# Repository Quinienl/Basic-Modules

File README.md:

These modules are tested

- Multiple
- Buffered Multiple
- Switch

These files can be used to build your own PCB's and Panels

More info on my site

[Quinie Basic Modules](https://www.quinie.nl/the-basic-modules/).

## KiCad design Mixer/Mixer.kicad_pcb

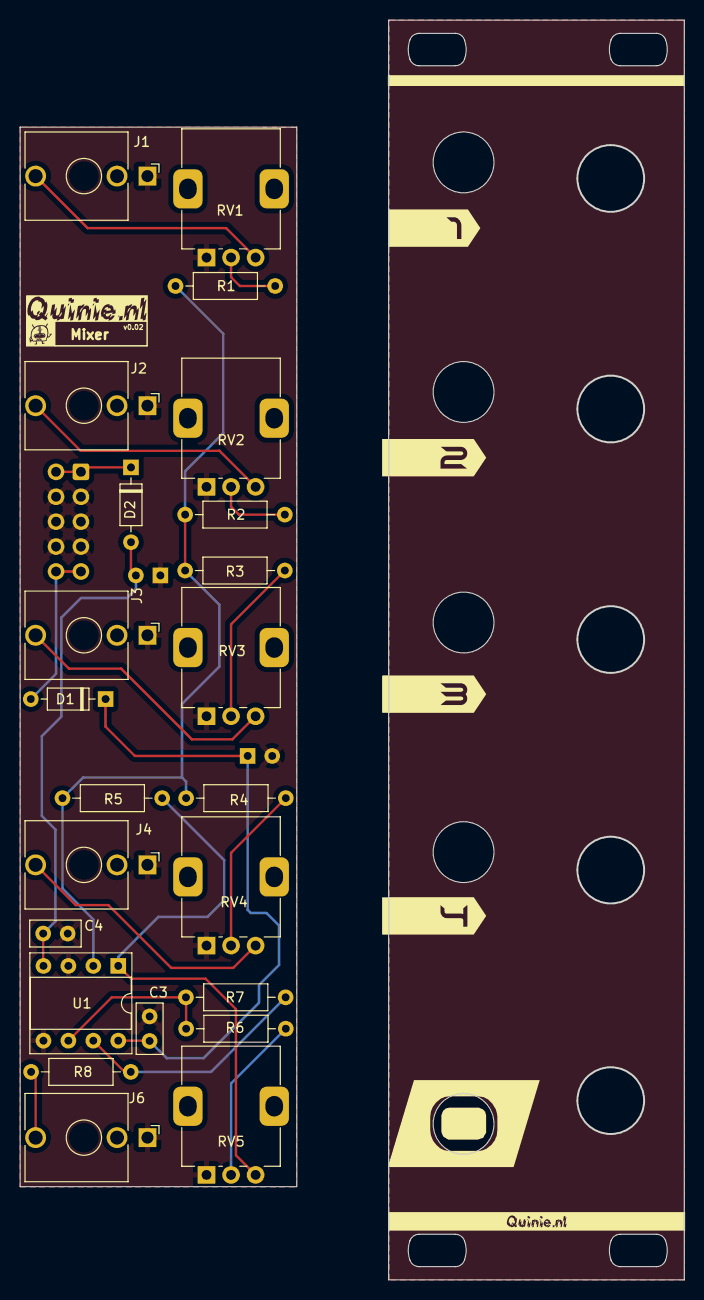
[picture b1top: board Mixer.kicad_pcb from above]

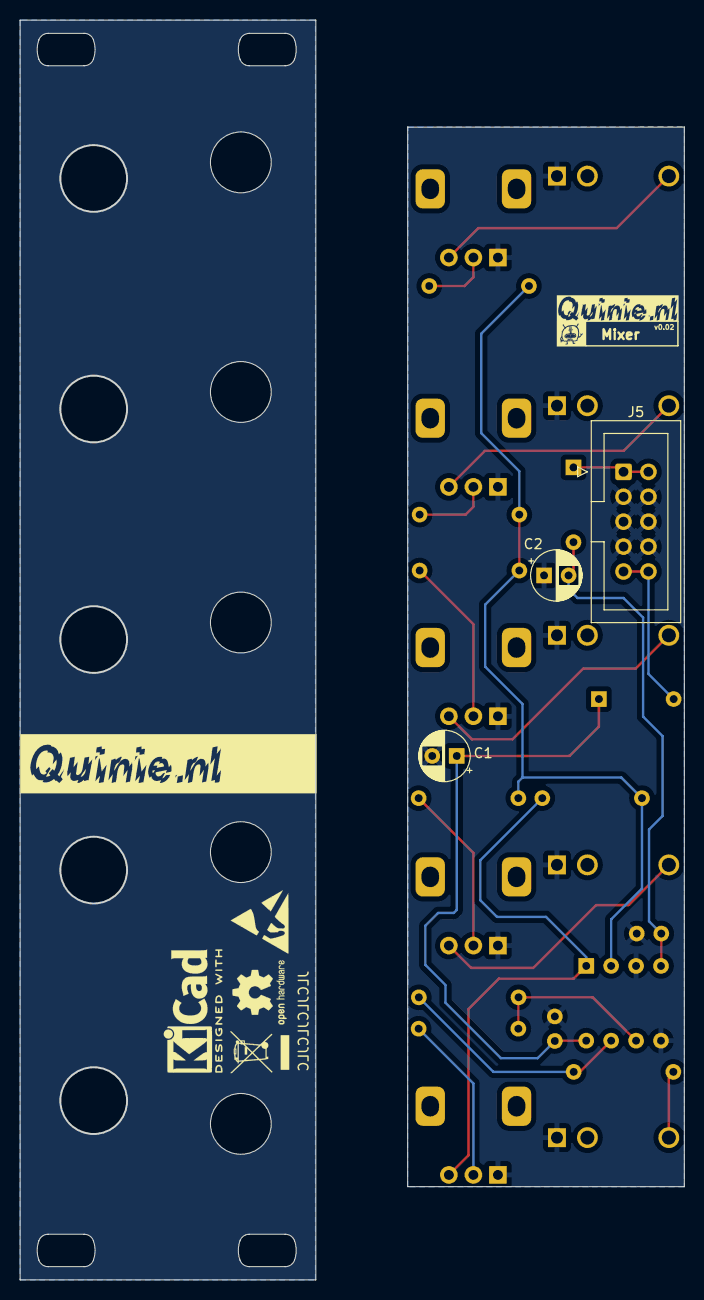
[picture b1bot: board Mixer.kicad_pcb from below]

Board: 2 copper layers, 67.6 x 128.3 mm, 38 parts (6 on the bottom side), 19 nets.

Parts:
C1, C2: 10uf; CP_Radial_D5.0mm_P2.50mm
C3, C4: C; C_Disc_D5.0mm_W2.5mm_P2.50mm
D1, D2: 1n4148; D_DO-35_SOD27_P7.62mm_Horizontal
J1, J2, J3, J4, J6: AudioJack2_SwitchT; Jack_3.5mm_QingPu_WQP-PJ398SM_Vertical_CircularHoles
J5: Conn_02x05_Odd_Even; IDC-Header_2x05_P2.54mm_Vertical
R1, R2, R3, R4, R5, R6, R7: 100k; R_Axial_DIN0207_L6.3mm_D2.5mm_P10.16mm_Horizontal
R8: 1k; R_Axial_DIN0207_L6.3mm_D2.5mm_P10.16mm_Horizontal
RV1, RV2, RV3, RV4, RV5: R_Potentiometer; Potentiometer_Alps_RK09K_Single_Vertical
U1: TL072; DIP-8_W7.62mm_Socket
kibuzzard-65A30B0C: G***; kibuzzard-65A30B0C
kibuzzard-65A30B02: G***; kibuzzard-65A30B02
kibuzzard-65A30B14: G***; kibuzzard-65A30B14
kibuzzard-65A30BCA: G***; kibuzzard-65A30BCA
kibuzzard-63729A5C, kibuzzard-63729A5C#2: G***; kibuzzard-63729A5C
kibuzzard-63947F16: G***; kibuzzard-63947F16
kibuzzard-63948EE9: G***; kibuzzard-63948EE9
kibuzzard-639724AE: G***; kibuzzard-639724AE
kibuzzard-63663374, kibuzzard-63663374#2: G***; kibuzzard-63663374
kibuzzard-63949171: G***; kibuzzard-63949171

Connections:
+12V: C1.1, C3.2, D1.1 (K), U1.8 (V+)
-12V: C2.2, C4.2, D2.2 (A), U1.4 (V-)
GND: C1.2, C2.1, C3.1, C4.1, J1.S, J2.S, J3.S, J4.S, J5.3, J5.4, J5.5, J5.6, J5.7, J5.8, J6.S, RV1.1, RV2.1, RV3.1, RV4.1, RV5.1, U1.3 (+), U1.5 (+)
unnamed: D1.2 (A), J5.9, J5.10
unnamed: D2.1 (K), J5.1, J5.2
unnamed: J1.T, RV1.3
unnamed: J2.T, RV2.3
unnamed: J3.T, RV3.3
unnamed: J4.T, RV4.3
unnamed: J6.T, R8.1
unnamed: R1.1, RV1.2
unnamed: R2.1, RV2.2
unnamed: R3.1, RV3.2
unnamed: R4.1, RV4.2
unnamed: R5.1, RV5.3, U1.1
unnamed: R6.1, RV5.2
unnamed: R7.1, R8.2, U1.7
unnamed: R1.2, R2.2, R3.2, R4.2, R5.2, U1.2 (-)
unnamed: R6.2, R7.2, U1.6 (-)

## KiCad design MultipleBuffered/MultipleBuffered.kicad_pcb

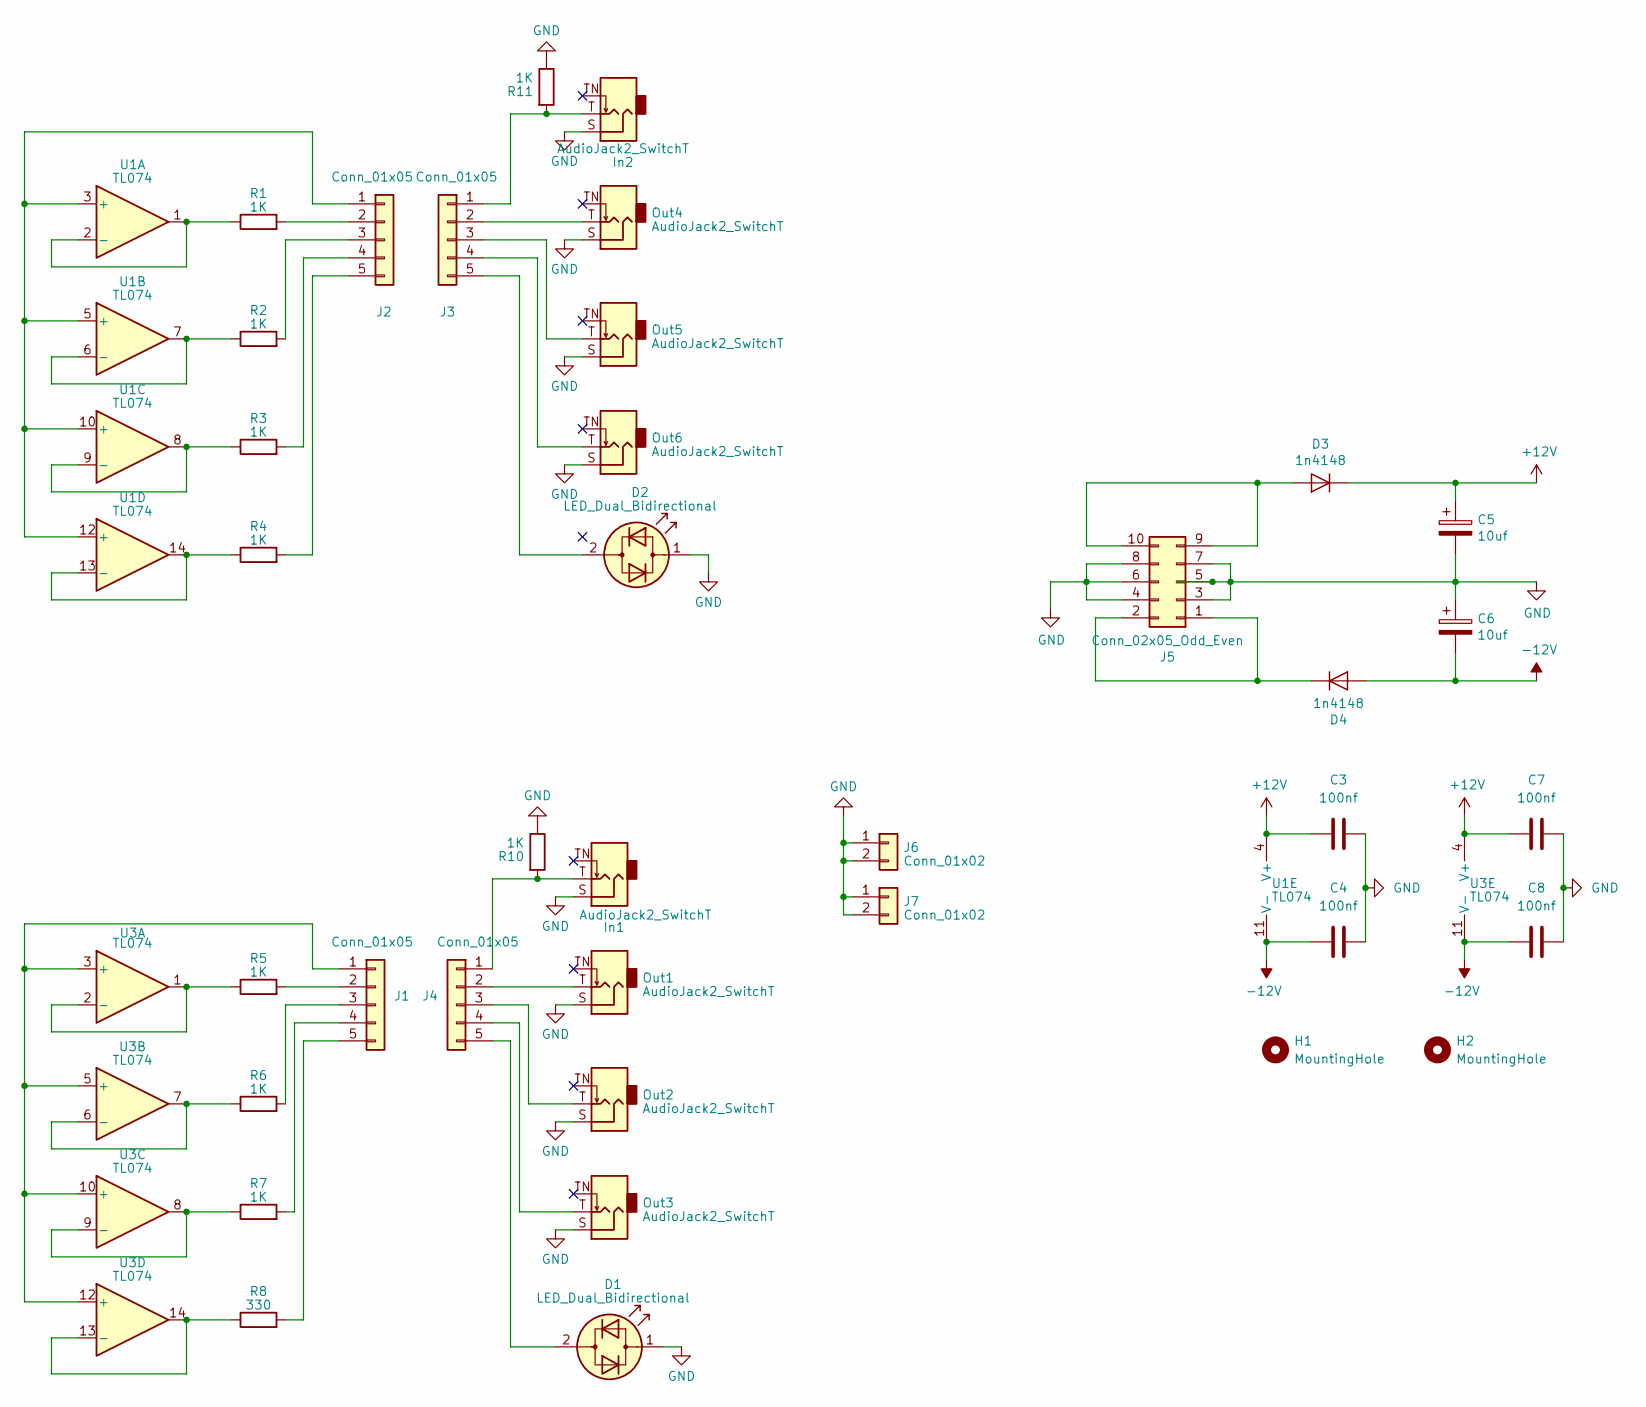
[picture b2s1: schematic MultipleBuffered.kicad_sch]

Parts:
C3, C4, C7, C8: 100nf; C_Disc_D5.0mm_W2.5mm_P2.50mm
C5, C6: 10uf; CP_Radial_D5.0mm_P2.50mm
D1, D2: LED_Dual_Bidirectional; LED_D3.0mm
D3, D4: 1n4148; D_DO-35_SOD27_P7.62mm_Horizontal
H1, H2: MountingHole; MountingHole_3.2mm_M3
In1, In2: AudioJack2_SwitchT; Jack_3.5mm_QingPu_WQP-PJ398SM_Vertical_CircularHoles
J1, J2: Conn_01x05; PinHeader_1x05_P2.54mm_Vertical
J3, J4: Conn_01x05; PinSocket_1x05_P2.54mm_Vertical
J5: Conn_02x05_Odd_Even; IDC-Header_2x05_P2.54mm_Vertical
J6: Conn_01x02; PinHeader_1x02_P2.54mm_Vertical
J7: Conn_01x02; PinSocket_1x02_P2.54mm_Vertical
Out1, Out2, Out3, Out4, Out5, Out6: AudioJack2_SwitchT; Jack_3.5mm_QingPu_WQP-PJ398SM_Vertical_CircularHoles
R1, R2, R3, R4, R5, R6, R7, R11: 1K; R_Axial_DIN0207_L6.3mm_D2.5mm_P7.62mm_Horizontal
R8: 330; R_Axial_DIN0207_L6.3mm_D2.5mm_P7.62mm_Horizontal
R10: 1K; R_Axial_DIN0207_L6.3mm_D2.5mm_P2.54mm_Vertical
U1, U3: TL074; DIP-14_W7.62mm_Socket

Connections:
+12V: C3.1, C5.1, C7.1, D3.1 (K), U1.4 (V+), U3.4 (V+)
-12V: C4.1, C6.2, C8.1, D4.2 (A), U1.11 (V-), U3.11 (V-)
GND: C3.2, C4.2, C5.2, C6.1, C7.2, C8.2, D1.1 (KA), D2.1 (KA), In1.S, In2.S, J5.3, J5.4, J5.5, J5.6, J5.7, J5.8, J6.1, J6.2, J7.1, J7.2, Out1.S, Out2.S, Out3.S, Out4.S, Out5.S, Out6.S, R10.1, R11.1
unnamed: D1.2 (AK), J4.5
unnamed: D2.2 (AK), J3.5
unnamed: D3.2 (A), J5.9, J5.10
unnamed: D4.1 (K), J5.1, J5.2
unnamed: J1.1, U3.3 (+), U3.5 (+), U3.10 (+), U3.12 (+)
unnamed: J1.2, R5.2
unnamed: J1.3, R6.2
unnamed: J1.4, R7.2
unnamed: J1.5, R8.2
unnamed: J2.1, U1.3 (+), U1.5 (+), U1.10 (+), U1.12 (+)
unnamed: J2.2, R1.2
unnamed: J2.3, R2.2
unnamed: J2.4, R3.2
unnamed: J2.5, R4.2
unnamed: In2.T, J3.1, R11.2
unnamed: J3.2, Out4.T
unnamed: J3.3, Out5.T
unnamed: J3.4, Out6.T
unnamed: In1.T, J4.1, R10.2
unnamed: J4.2, Out1.T
unnamed: J4.3, Out2.T
unnamed: J4.4, Out3.T
unnamed: R1.1, U1.1, U1.2 (-)
unnamed: R2.1, U1.6 (-), U1.7
unnamed: R3.1, U1.8, U1.9 (-)
unnamed: R4.1, U1.13 (-), U1.14
unnamed: R5.1, U3.1, U3.2 (-)
unnamed: R6.1, U3.6 (-), U3.7
unnamed: R7.1, U3.8, U3.9 (-)
unnamed: R8.1, U3.13 (-), U3.14

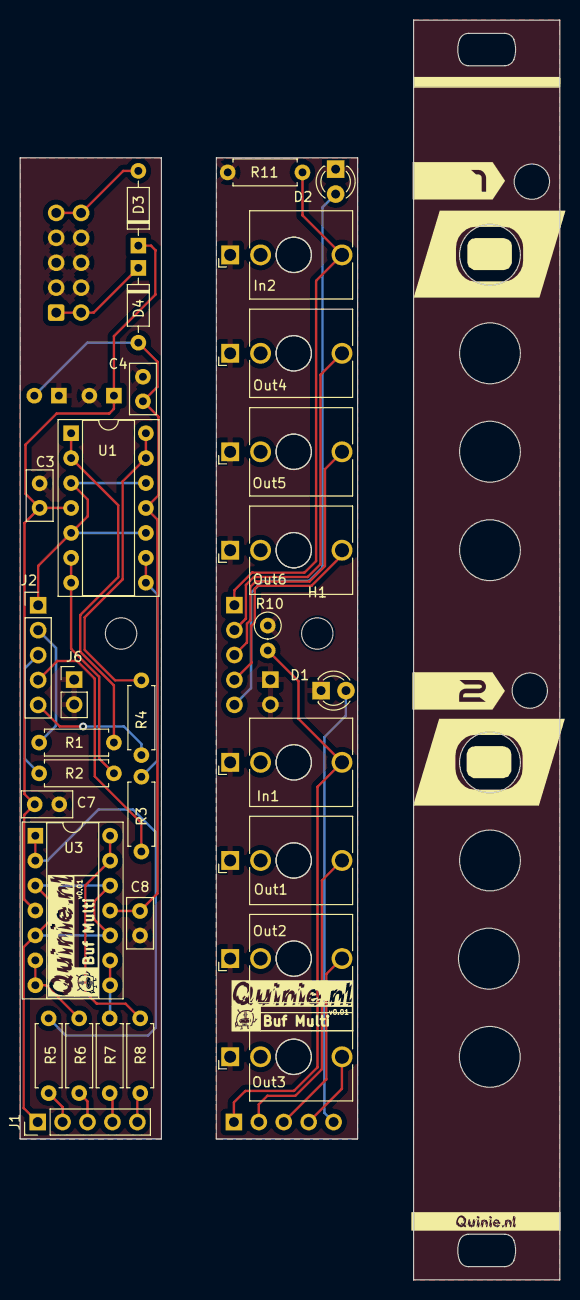
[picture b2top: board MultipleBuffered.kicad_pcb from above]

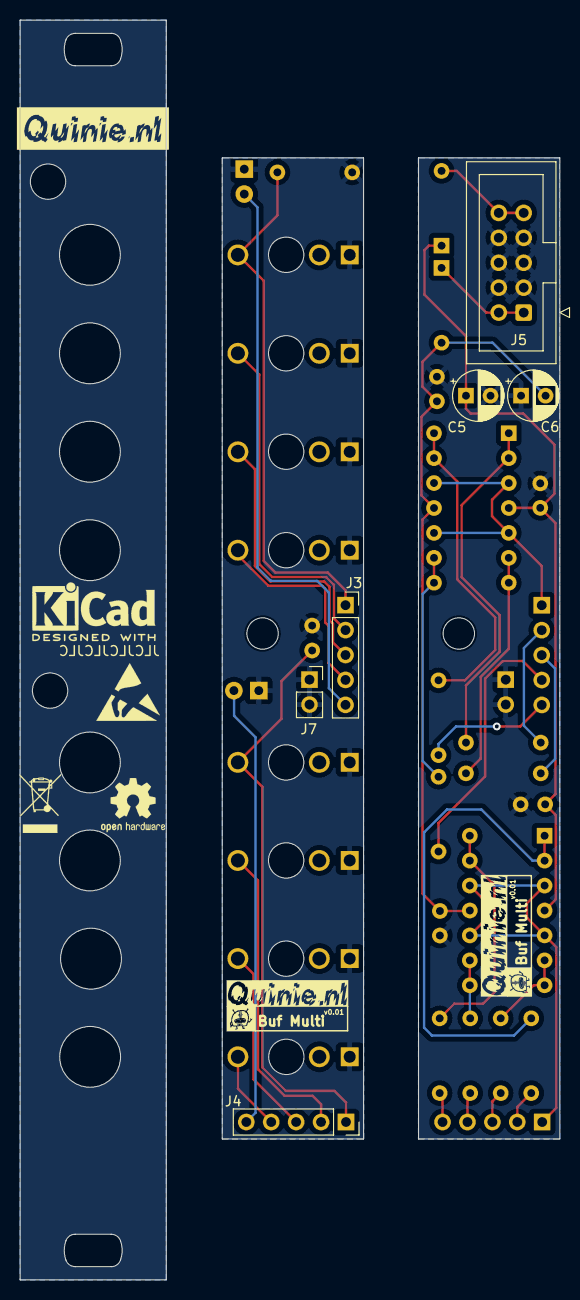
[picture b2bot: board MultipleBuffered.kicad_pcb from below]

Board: 2 copper layers, 55.0 x 128.4 mm, 54 parts (11 on the bottom side), 33 nets.

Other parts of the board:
kibuzzard-656B60C2: G***; kibuzzard-656B60C2
kibuzzard-656B617B: G***; kibuzzard-656B617B
kibuzzard-656CA602: G***; kibuzzard-656CA602
kibuzzard-656CA711: G***; kibuzzard-656CA711
kibuzzard-63729A5C, kibuzzard-63729A5C#2, kibuzzard-63729A5C#3, kibuzzard-63729A5C#4: G***; kibuzzard-63729A5C
kibuzzard-63948EE9: G***; kibuzzard-63948EE9
kibuzzard-63663374, kibuzzard-63663374#2, kibuzzard-63663374#3, kibuzzard-63663374#4: G***; kibuzzard-63663374
kibuzzard-63949171, kibuzzard-63949171#2: G***; kibuzzard-63949171

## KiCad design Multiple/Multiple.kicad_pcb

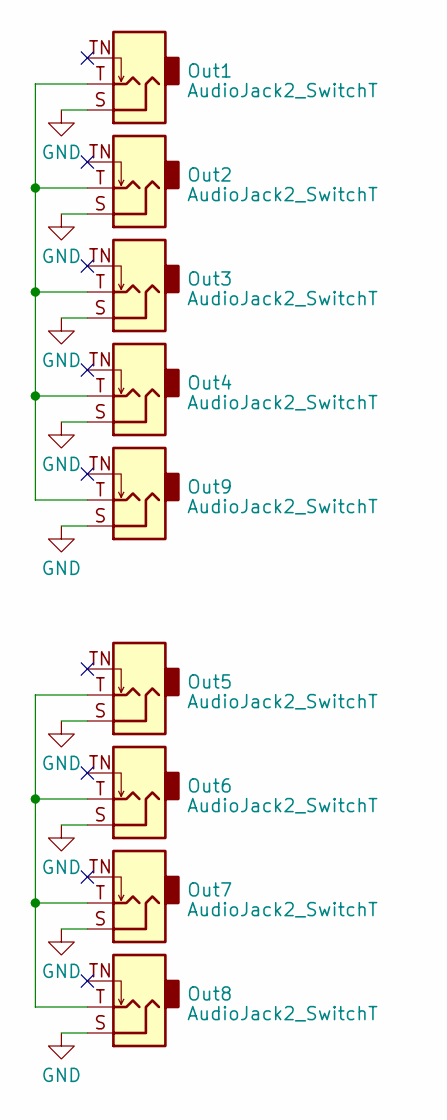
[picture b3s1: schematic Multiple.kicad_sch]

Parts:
Out1, Out2, Out3, Out4, Out5, Out6, Out7, Out8, Out9: AudioJack2_SwitchT; Jack_3.5mm_QingPu_WQP-PJ398SM_Vertical_CircularHoles

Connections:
GND: Out1.S, Out2.S, Out3.S, Out4.S, Out5.S, Out6.S, Out7.S, Out8.S, Out9.S
unnamed: Out1.T, Out2.T, Out3.T, Out4.T, Out9.T
unnamed: Out5.T, Out6.T, Out7.T, Out8.T

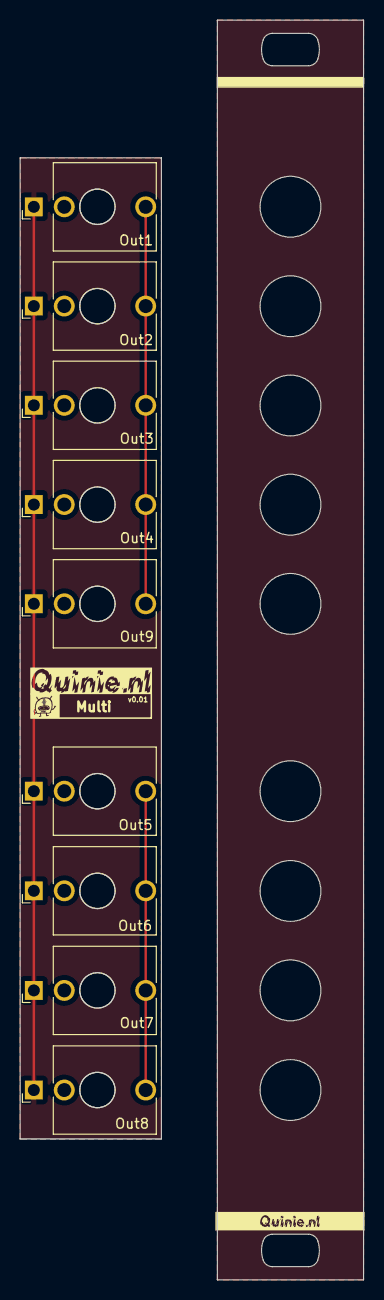
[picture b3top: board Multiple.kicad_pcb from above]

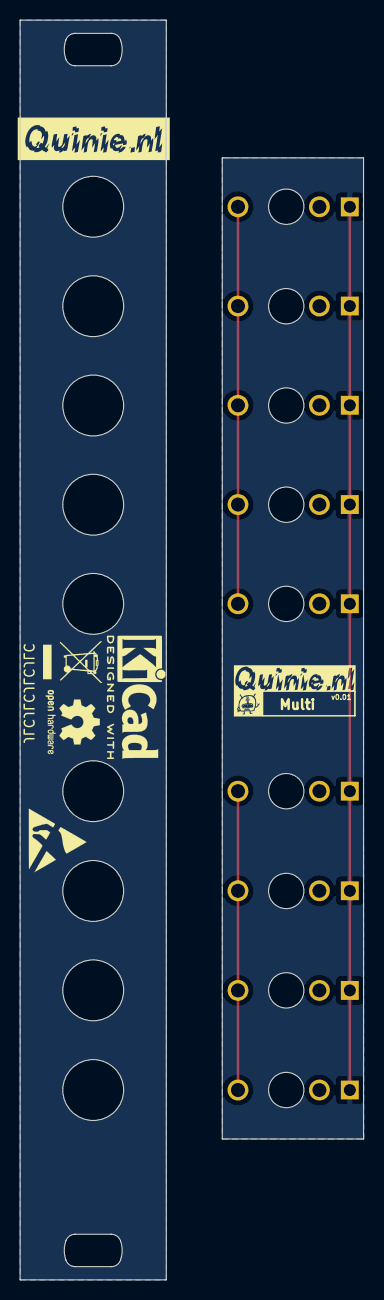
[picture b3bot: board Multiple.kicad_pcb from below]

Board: 2 copper layers, 35.0 x 128.4 mm, 16 parts (3 on the bottom side), 3 nets.

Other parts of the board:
kibuzzard-656B60C2: G***; kibuzzard-656B60C2
kibuzzard-656B617B: G***; kibuzzard-656B617B
kibuzzard-656B6089: G***; kibuzzard-656B6089
kibuzzard-63729A5C, kibuzzard-63729A5C#2: G***; kibuzzard-63729A5C
kibuzzard-63663374, kibuzzard-63663374#2: G***; kibuzzard-63663374

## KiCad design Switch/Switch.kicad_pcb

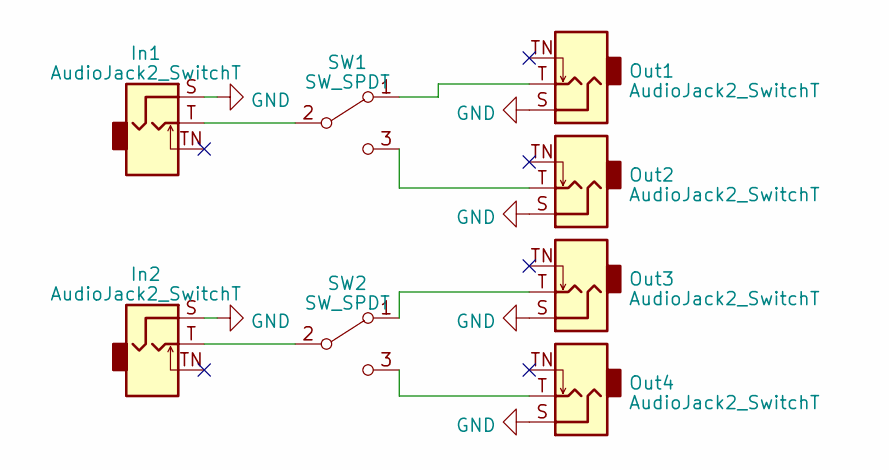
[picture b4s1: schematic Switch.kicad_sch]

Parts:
In1, In2: AudioJack2_SwitchT; Jack_3.5mm_QingPu_WQP-PJ398SM_Vertical_CircularHoles
Out1, Out2, Out3, Out4: AudioJack2_SwitchT; Jack_3.5mm_QingPu_WQP-PJ398SM_Vertical_CircularHoles
SW1, SW2: SW_SPDT; SW_100SP3T1B1M2QEH

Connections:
GND: In1.S, In2.S, Out1.S, Out2.S, Out3.S, Out4.S
unnamed: Out1.T, SW1.1 (A)
unnamed: In1.T, SW1.2 (B)
unnamed: Out2.T, SW1.3 (C)
unnamed: Out3.T, SW2.1 (A)
unnamed: In2.T, SW2.2 (B)
unnamed: Out4.T, SW2.3 (C)

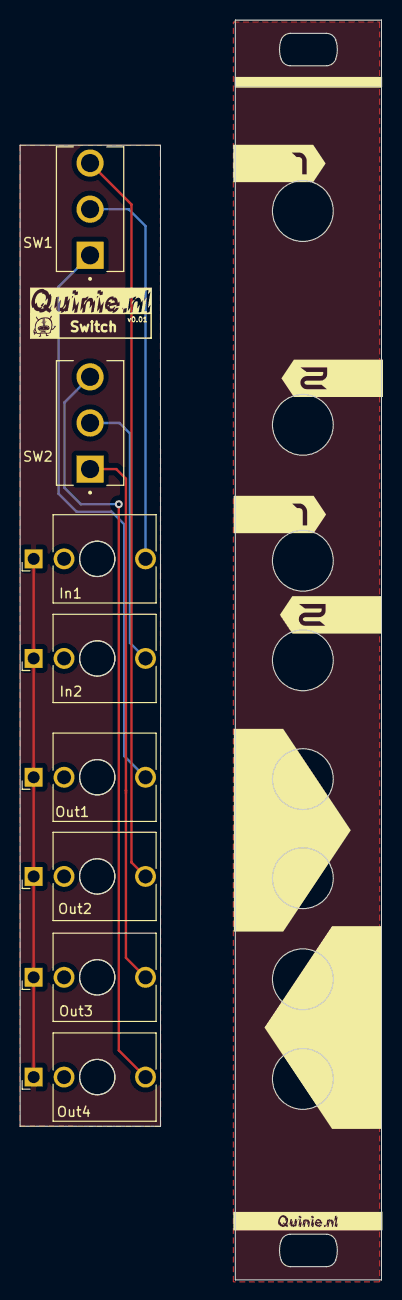
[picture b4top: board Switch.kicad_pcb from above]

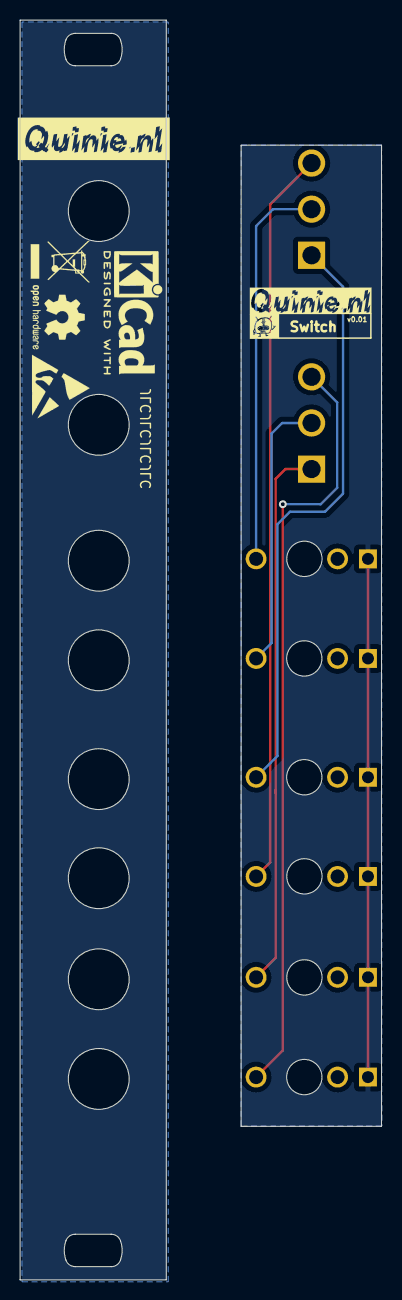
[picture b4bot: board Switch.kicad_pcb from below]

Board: 2 copper layers, 36.8 x 128.4 mm, 21 parts (3 on the bottom side), 7 nets.

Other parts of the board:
kibuzzard-656B60C2: G***; kibuzzard-656B60C2
kibuzzard-656B617B: G***; kibuzzard-656B617B
kibuzzard-656C56A9: G***; kibuzzard-656C56A9
kibuzzard-63729A5C, kibuzzard-63729A5C#2: G***; kibuzzard-63729A5C
kibuzzard-63920CDF, kibuzzard-63920CDF#2: G***; kibuzzard-63920CDF
kibuzzard-63948EC7, kibuzzard-63948EC7#2: G***; kibuzzard-63948EC7
kibuzzard-63948EE9, kibuzzard-63948EE9#2: G***; kibuzzard-63948EE9
kibuzzard-63663374, kibuzzard-63663374#2: G***; kibuzzard-63663374

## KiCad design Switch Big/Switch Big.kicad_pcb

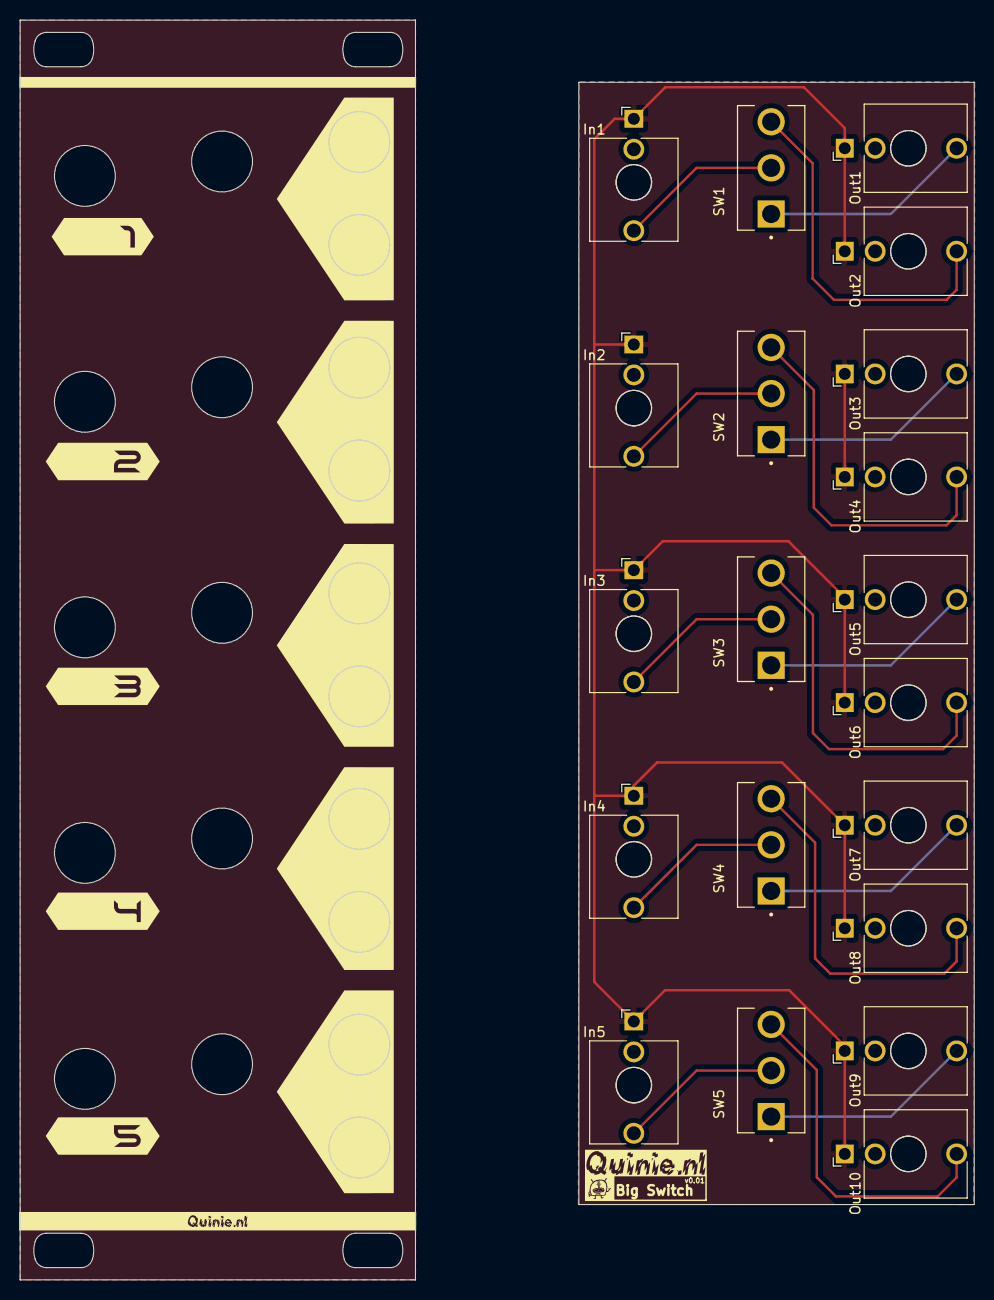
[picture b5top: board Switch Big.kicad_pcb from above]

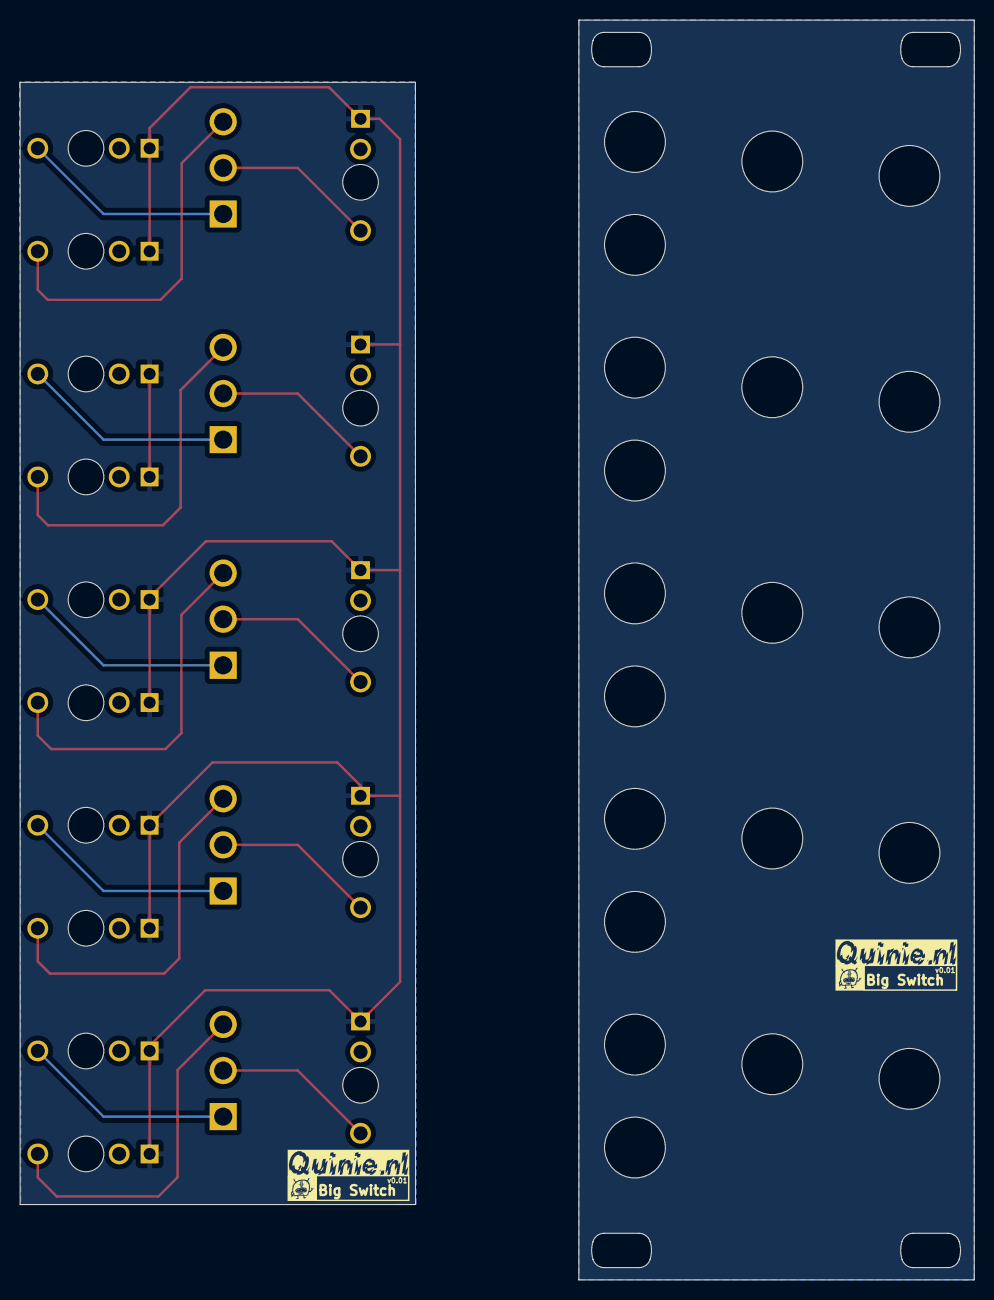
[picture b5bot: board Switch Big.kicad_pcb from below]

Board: 2 copper layers, 97.3 x 128.4 mm, 38 parts (4 on the bottom side), 16 nets.

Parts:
In1, In2, In3, In4, In5: AudioJack2_SwitchT; Jack_3.5mm_QingPu_WQP-PJ398SM_Vertical_CircularHoles
Out1, Out2, Out3, Out4, Out5, Out6, Out7, Out8, Out9, Out10: AudioJack2_SwitchT; Jack_3.5mm_QingPu_WQP-PJ398SM_Vertical_CircularHoles
SW1, SW2, SW3, SW4, SW5: SW_SPDT; SW_100SP3T1B1M2QEH
kibuzzard-6564ECD4: G***; kibuzzard-6564ECD4
kibuzzard-6564ED25: G***; kibuzzard-6564ED25
kibuzzard-63729A5C, kibuzzard-63729A5C#2, kibuzzard-63729A5C#3: G***; kibuzzard-63729A5C
kibuzzard-63920CDF, kibuzzard-63920CDF#2, kibuzzard-63920CDF#3, kibuzzard-63920CDF#4, kibuzzard-63920CDF#5: G***; kibuzzard-63920CDF
kibuzzard-65662F7A: G***; kibuzzard-65662F7A
kibuzzard-65662F7F: G***; kibuzzard-65662F7F
kibuzzard-65662F15: G***; kibuzzard-65662F15
kibuzzard-65662F83: G***; kibuzzard-65662F83
kibuzzard-65662F89: G***; kibuzzard-65662F89
kibuzzard-63663374, kibuzzard-63663374#2, kibuzzard-63663374#3: G***; kibuzzard-63663374

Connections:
GND: In1.S, In2.S, In3.S, In4.S, In5.S, Out1.S, Out2.S, Out3.S, Out4.S, Out5.S, Out6.S, Out7.S, Out8.S, Out9.S, Out10.S
unnamed: Out1.T, SW1.1 (A)
unnamed: In1.T, SW1.2 (B)
unnamed: Out2.T, SW1.3 (C)
unnamed: Out3.T, SW2.1 (A)
unnamed: In2.T, SW2.2 (B)
unnamed: Out4.T, SW2.3 (C)
unnamed: Out5.T, SW3.1 (A)
unnamed: In3.T, SW3.2 (B)
unnamed: Out6.T, SW3.3 (C)
unnamed: Out7.T, SW4.1 (A)
unnamed: In4.T, SW4.2 (B)
unnamed: Out8.T, SW4.3 (C)
unnamed: Out9.T, SW5.1 (A)
unnamed: In5.T, SW5.2 (B)
unnamed: Out10.T, SW5.3 (C)

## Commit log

2023-11-27 First
2023-11-27 Fixed kicad issues
2023-11-28 Fills
2023-12-14 Mixer
2023-12-14 Update pcb
2023-12-16 Update Tested
